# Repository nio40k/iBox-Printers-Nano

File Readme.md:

Hello all! 

I used to work for iBox Printers up until the point it closed. And now that it has closed, I wish to release the source code to the community to help improve the printer and make the community happier with their product. I do appologiese to those who did not recieve a printer and had a hard time with the company. I hope that this will help make you happier. With that being said here is what these folder contain. 

The folder labled "Nano ibox folder" is the ibox directory of the printer. This one contains the source code as well as the complied file as up to date since I was let go from the company. There are also some print packages that were left in there since this is a direct copy of my personal printer I used to develop with for the company. The main file that runs the printer is called "iBoxPrintManager.py" and the web GUI file is called "iBoxWebGUI.js". 

In the folder labled "PCB Files" there are the Eagle PCB layout files for the printer's PCB. There are also pick and place files in there which we used for the surface mount componentes. Also for those of you that used Altium, there is a folder which has the board which was converted from Eagle. 

And finally, I have made a direct image dump from my personal development printer. Here is the link to download: https://drive.google.com/file/d/0B6_silB01EPpQ0lyNnV3Z2VMd0U/view?usp=sharing . This should be ok to flash driectly to your printer and might fix any isses that is software related. This came from an 8 GB Micro SD card so you will need to use at least an 8 GB card or higher. 

I hope that this helps the community! 

Sincerely,
Fox

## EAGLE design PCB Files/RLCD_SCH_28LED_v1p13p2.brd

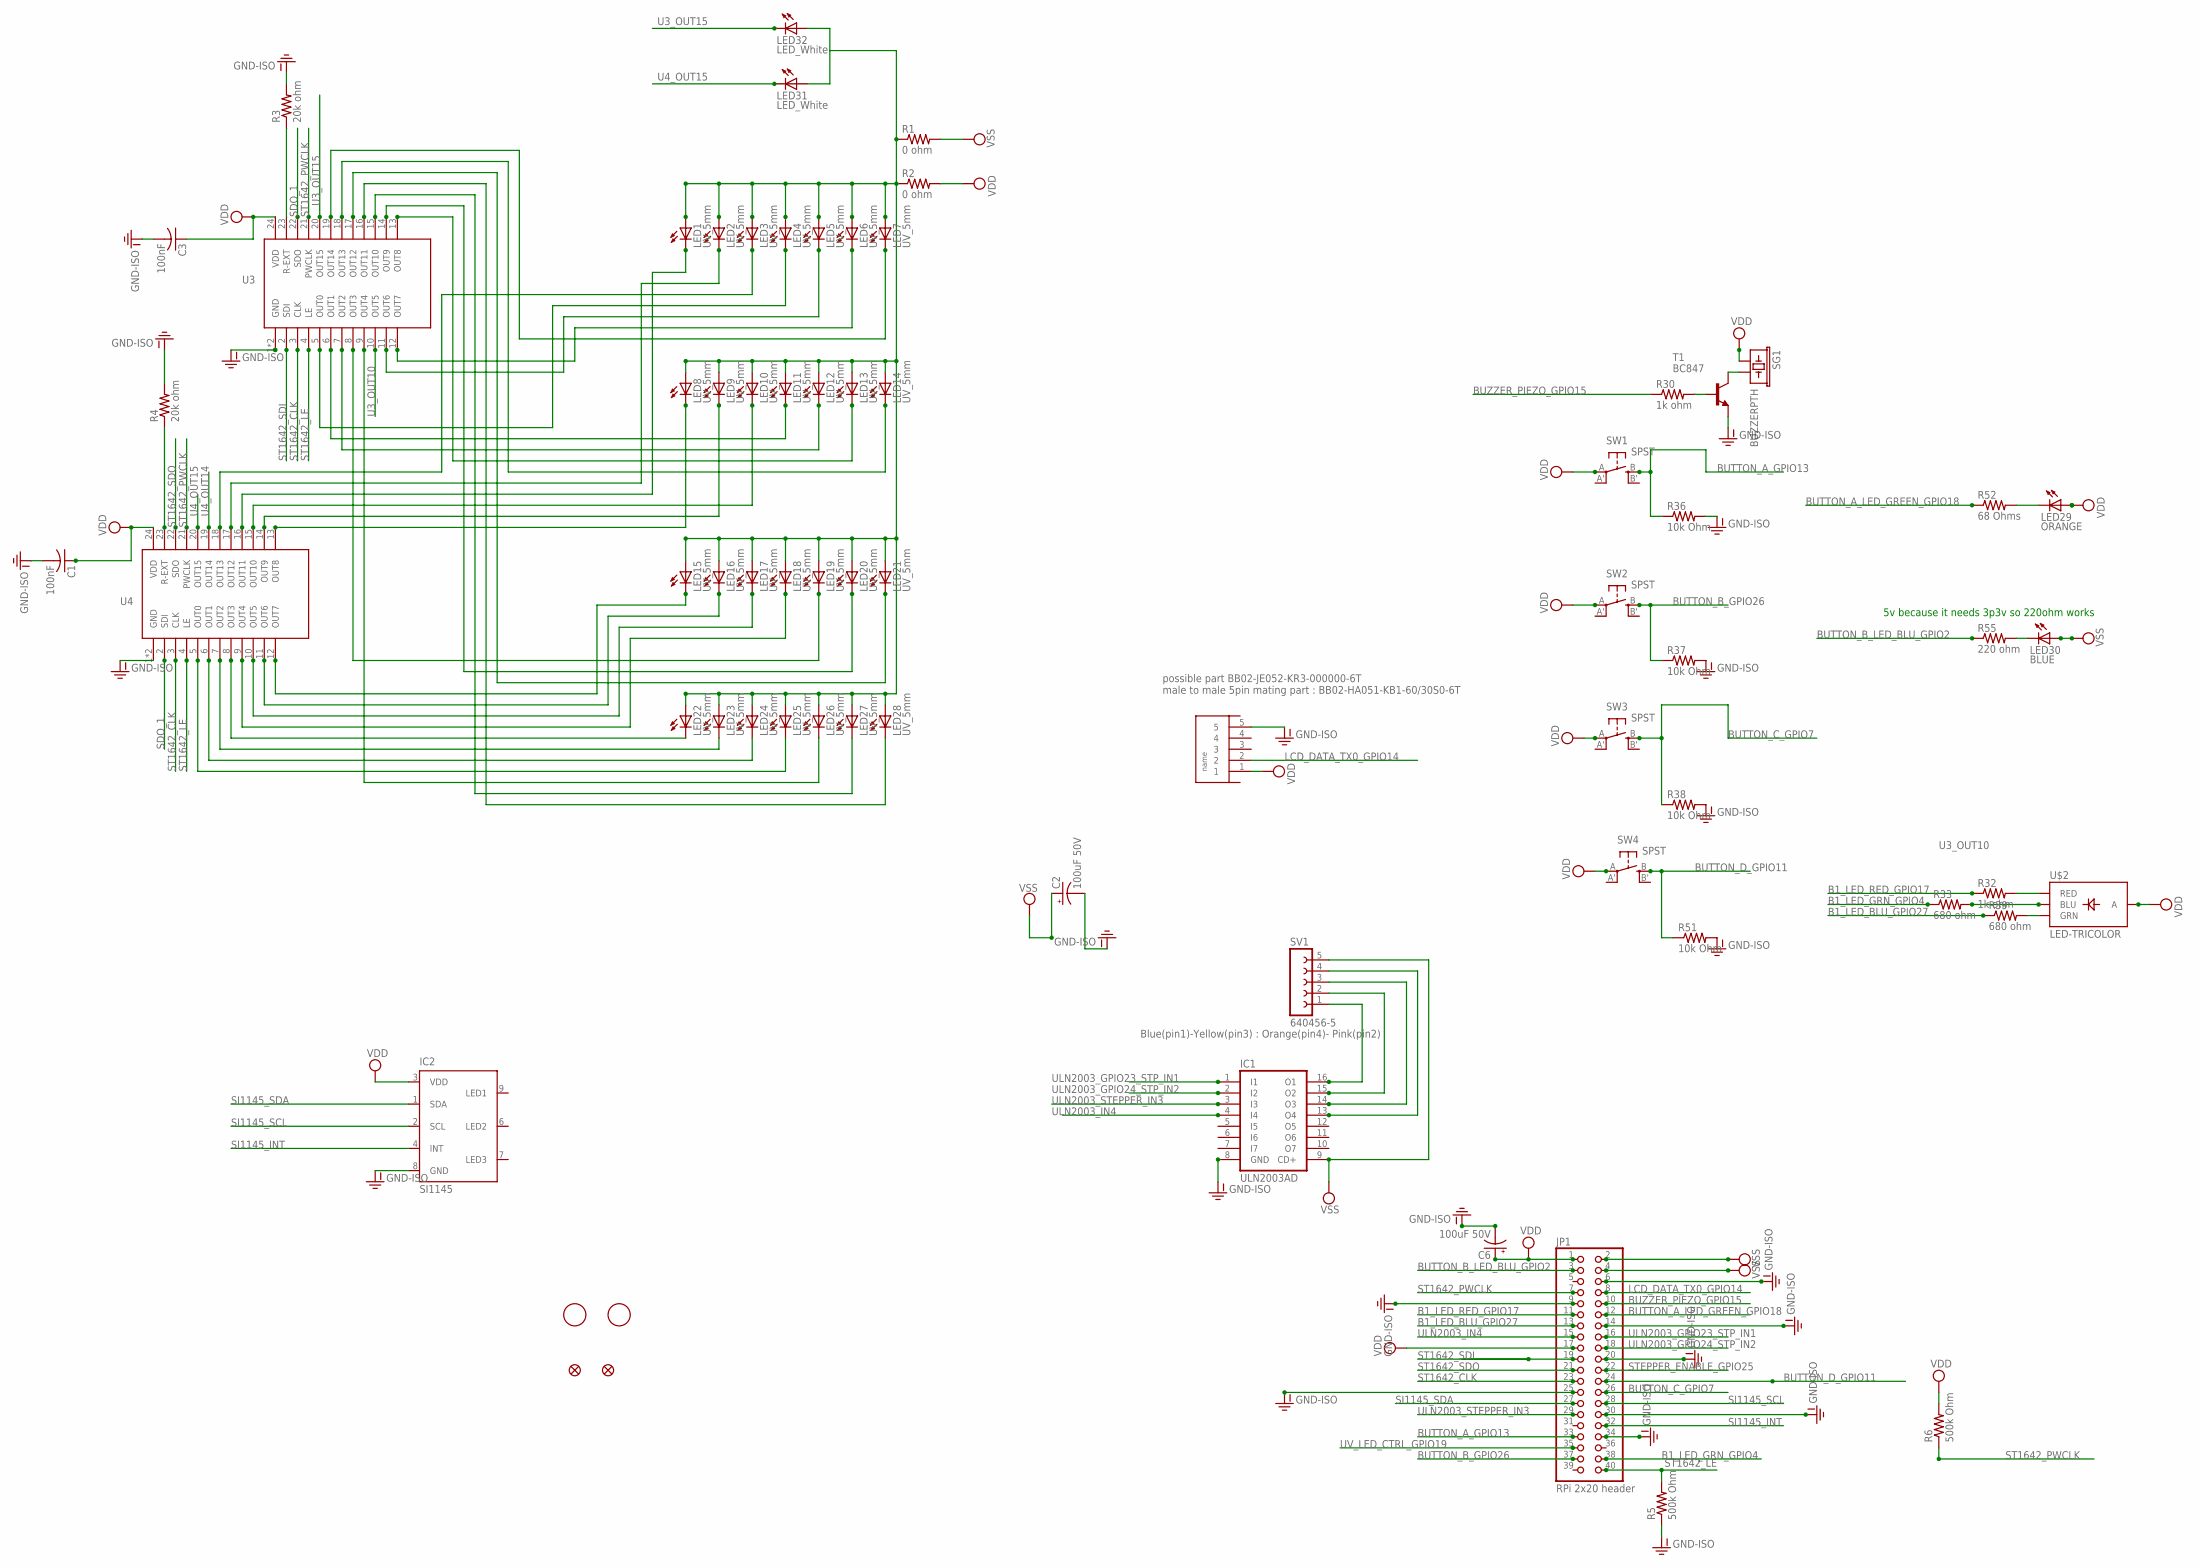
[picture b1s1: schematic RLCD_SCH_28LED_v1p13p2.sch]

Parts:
C1, C3: 100nF; C0805
C2, C6: 100uF 50V; E3,5-8; PARTNO REA101M1HBK-0811P
FID1, FID2: FIDUCIAL1X2; FIDUCIAL-1X2
IC1: ULN2003AD; SO16
IC2: SI1145; QFN-10
JP1: RPi 2x20 header; 2X20; PARTNO 929975-01-13-RK
LED1, LED2, LED3, LED4, LED5, LED6, LED7, LED8, LED9, LED10, LED11, LED12, LED13, LED14, LED15, LED16, LED17, LED18, LED19, LED20, LED21, LED22, LED23, LED24, LED25, LED26, LED27, LED28: UV_5mm; LED5MM; PARTNO *
LED29: ORANGE; CHIPLED_1206; PARTNO LG N971-KN-1
LED30: BLUE; CHIPLED_1206; PARTNO LTST-C21TBKT
LED31, LED32: LED_White; CHIPLED_1206; PARTNO LG N971-KN-1
R1, R2: 0 ohm; 0805; PARTNO DNP
R3, R4: 20k ohm; 0805; PARTNO DNP
R5, R6: 500k Ohm; 0805; PARTNO RK73B2ATTD103J
R30, R32: 1k ohm; 0805; PARTNO RK73H2ATTD1001F
R33, R39: 680 ohm; 0805; PARTNO RK73B2ATTD681J
R36, R37, R38, R51: 10k Ohm; 0805; PARTNO RK73B2ATTD103J
R52: 68 Ohms; 0805; PARTNO RK73B2ATTDD121J
R55: 220 ohm; 0805; PARTNO RK73B2ATTD221J
SG1: BUZZERPTH; BUZZER-12MM; PARTNO AT-1220-TT-R
SV1: 640456-5; FE05-1; PARTNO 640456-5
SV3_LCD_HEADER: 22-05-2051; MDF7-5S-2.54DSA; PARTNO MDF7-5S-2.54DSA(55)
SW1, SW2, SW3, SW4: SPST; EVQ-Q2
T1: BC847; SOT23; PARTNO MMUN2214LT1G
U$1, U$5: FIDUCIAL; FIDUCIAL_1MM
U$2: LED-TRICOLOR; LED-TRICOLOR-SMD; PARTNO CLV1A-FKB-CHMKPEHBB7A363
U$3, U$4: LED1642GWTTR; TSSOP24

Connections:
B1_LED_BLU_GPIO27: JP1.13, R39.1
B1_LED_GRN_GPIO4: JP1.38, R33.1
B1_LED_RED_GPIO17: JP1.11, R32.1
BUTTON_A_GPIO13: JP1.33, R36.1, SW1.B (S)
BUTTON_A_LED_GREEN_GPIO18: JP1.12, R52.1
BUTTON_B_GPIO26: JP1.37, R37.1, SW2.B (S)
BUTTON_B_LED_BLU_GPIO2: JP1.3, R55.1
BUTTON_C_GPIO7: JP1.26, R38.1, SW3.B (S)
BUTTON_D_GPIO11: JP1.24, R51.1, SW4.B (S)
BUZZER_PIEZO_GPIO15: JP1.10, R30.1
GND-ISO: C1.2, C2.-, C3.2, C6.-, IC1.8 (GND), IC2.8 (GND), JP1.6, JP1.9, JP1.14, JP1.20, JP1.25, JP1.30, JP1.34, R3.2, R4.2, R5.1, R36.2, R37.2, R38.2, R51.2, SV3_LCD_HEADER.5, T1.2 (E), U$3.1 (GND), U$3.P$100 (GND), U$4.1 (GND), U$4.P$100 (GND)
LCD_DATA_TX0_GPIO14: JP1.8, SV3_LCD_HEADER.2
LED+: LED1.A, LED2.A, LED3.A, LED4.A, LED5.A, LED6.A, LED7.A, LED8.A, LED9.A, LED10.A, LED11.A, LED12.A, LED13.A, LED14.A, LED15.A, LED16.A, LED17.A, LED18.A, LED19.A, LED20.A, LED21.A, LED22.A, LED23.A, LED24.A, LED25.A, LED26.A, LED27.A, LED28.A, LED31.A, LED32.A, R1.1, R2.1
unnamed: LED2.K (C), U$4.17 (OUT12)
unnamed: LED3.K (C), U$4.18 (OUT13)
unnamed: LED6.K (C), U$3.12 (OUT7)
unnamed: LED4.K (C), U$3.5 (OUT0)
unnamed: LED5.K (C), U$3.11 (OUT6)
unnamed: LED22.K (C), U$4.8 (OUT3)
unnamed: LED15.K (C), U$4.12 (OUT7)
unnamed: R3.1, U$3.23 (R-EXT)
unnamed: LED16.K (C), U$4.11 (OUT6)
unnamed: LED17.K (C), U$4.10 (OUT5)
unnamed: LED18.K (C), U$4.9 (OUT4)
unnamed: R4.1, U$4.23 (R-EXT)
unnamed: LED19.K (C), U$3.8 (OUT3)
unnamed: LED11.K (C), U$3.6 (OUT1)
unnamed: LED9.K (C), U$4.14 (OUT9)
unnamed: LED10.K (C), U$4.15 (OUT10)
unnamed: LED20.K (C), U$3.14 (OUT9)
unnamed: LED12.K (C), U$3.7 (OUT2)
unnamed: R39.2, U$2.G (GRN)
unnamed: LED14.K (C), U$3.18 (OUT13)
unnamed: LED21.K (C), U$3.17 (OUT12)
unnamed: LED23.K (C), U$4.7 (OUT2)
unnamed: LED24.K (C), U$4.6 (OUT1)
unnamed: LED25.K (C), U$4.5 (OUT0)
unnamed: LED26.K (C), U$3.9 (OUT4)
unnamed: LED27.K (C), U$3.15 (OUT10)
unnamed: LED28.K (C), U$3.16 (OUT11)
unnamed: LED13.K (C), U$3.13 (OUT8)
unnamed: R30.2, T1.1 (B)
unnamed: IC1.13 (O4), SV1.4
unnamed: SG1.- (2), T1.3 (C)
unnamed: LED7.K (C), U$3.19 (OUT14)
unnamed: R33.2, U$2.B (BLU)
unnamed: IC1.14 (O3), SV1.3
unnamed: LED29.C, R52.2
unnamed: LED30.C, R55.2
unnamed: LED8.K (C), U$4.13 (OUT8)
unnamed: LED1.K (C), U$4.16 (OUT11)
unnamed: IC1.16 (O1), SV1.1
unnamed: IC1.15 (O2), SV1.2
SDO_1: U$3.22 (SDO), U$4.2 (SDI)
SI1145_INT: IC2.4 (INT), JP1.32
SI1145_SCL: IC2.2 (SCL), JP1.28
SI1145_SDA: IC2.1 (SDA), JP1.27
ST1642_CLK: JP1.23, U$3.3 (CLK), U$4.3 (CLK)
ST1642_LE: JP1.40, R5.2, U$3.4 (LE), U$4.4 (LE)
ST1642_PWCLK: JP1.7, R6.1, U$3.21 (PWCLK), U$4.21 (PWCLK)
ST1642_SDI: JP1.19, U$3.2 (SDI)
ST1642_SDO: JP1.21, U$4.22 (SDO)
STEPPER_ENABLE_GPIO25: JP1.22
U3_OUT10: R32.2, U$2.R (RED), U$3.10 (OUT5)
U3_OUT15: LED32.C, U$3.20 (OUT15)
U4_OUT14: U$4.19 (OUT14)
U4_OUT15: LED31.C, U$4.20 (OUT15)
ULN2003_GPIO23_STP_IN1: IC1.1 (I1), JP1.16
ULN2003_GPIO24_STP_IN2: IC1.2 (I2), JP1.18
ULN2003_IN4: IC1.4 (I4), JP1.15
ULN2003_STEPPER_IN3: IC1.3 (I3), JP1.29
UV_LED_CTRL_GPIO19: JP1.35
VDD: C1.1, C3.1, C6.+, IC2.3 (VDD), JP1.1, JP1.17, LED29.A, R2.2, R6.2, SG1.+ (1), SV3_LCD_HEADER.1, SW1.A, SW2.A, SW3.A, SW4.A, U$2.A, U$3.24 (VDD), U$4.24 (VDD)
VSS: C2.+, IC1.9 (CD+), JP1.2, JP1.4, LED30.A, R1.2, SV1.5

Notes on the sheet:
5v because it needs 3p3v so 220ohm works
Blue(pin1)-Yellow(pin3) : Orange(pin4)- Pink(pin2)
possible part BB02-JE052-KR3-000000-6T male to male 5pin mating part : BB02-HA051-KB1-60/30S0-6T

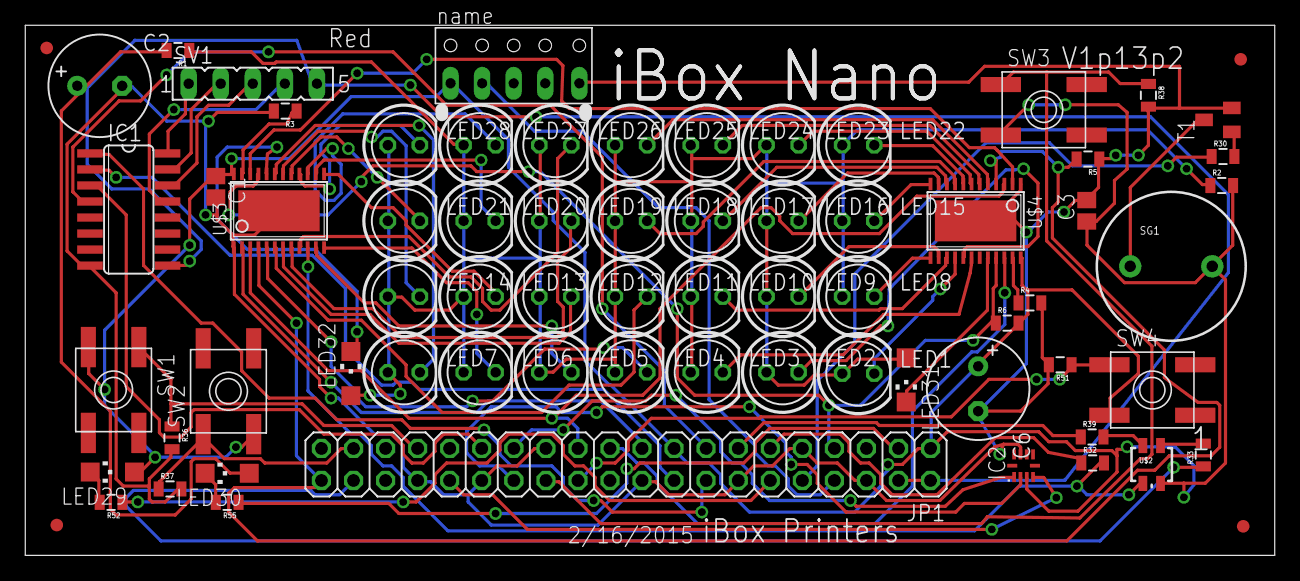
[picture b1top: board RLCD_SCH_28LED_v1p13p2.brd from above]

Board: 2 copper layers, 99.0 x 42.0 mm, 70 parts (0 on the bottom side), 71 nets.

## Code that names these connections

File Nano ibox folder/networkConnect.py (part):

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
bSoundEnabled = TRUE

# BUZZER_PIEZO_GPIO15
gpio_sound_piezo_element = 15

BUTTON_B_LED_BLU = 2#18 #2 #v1p5p0
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gpio_stepper_pin_button_down = 13 #10# Moving to GPIO 13 to free up SPI for LED driver : was10 #Move Z Down manually
# BUTTON_B_GPIO9              26 for SPI : 9 for pre 1p12p13 PCBs
gpio_stepper_pin_button_up = 26# 9 #Moving to GPIO26 to free up SDIO for ST LED1642 ::  ##Move Z Up Manually
# BUTTON_C_GPIO7              
gpio_stepper_pin_button_endstop = 7# 7 #Physical Microswitch indicating Z has hit its maximum travel.
bUse_Endstop = False #1=use endstop in printing and DOWN button, also in stepper Step. 0=Ignore. Created for Beta 4 which seems to have a bad GPIO7 :(
# BUTTON_D_GPIO11              
gpio_stepper_pin_button_print = 8 # switched because it is low at boot with UV LED : 11 #Start print job, if printing then Pause, hold down to Cancel print job

# UV_LED_CTRL_GPIO8       19 for SPI : 11 for pre 1p12p13 PCBs
gpio_stepper_pin_led_UV = 19#11 #Move to GPIO19 to free up SPI for ST LED1642 :: switched because 8 was HOT at boot : 8 #Activates UV LED. But not used anymore because UV_LED is controlled over SPI on the LED1642 chip

gpio_stepper_pin_led_red_B1 = 27# 2/1/15 PCB 1p12p30 : was 16#4##27 #4 #RGB 4,17,27
# B1_LED_GRN_GPIO4
gpio_stepper_pin_led_green_B1 = 20# 2/1/15 PCB 1p12p30 : was 27##17 #9/4/14==red
# B1_LED_BLU_GPIO27
gpio_stepper_pin_led_blue_B1 = 17##4 #27 #9/4/14==red

#SPI
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
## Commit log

2016-02-06 init

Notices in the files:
parts and their libraries:
SparkFun-Passives: Licensing: Creative Commons ShareAlike 4.0 International - https://creativecommons.org/licenses/by-sa/4.0
